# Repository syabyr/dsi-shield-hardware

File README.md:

# dsi-shield-hardware
dsi-shield hardware

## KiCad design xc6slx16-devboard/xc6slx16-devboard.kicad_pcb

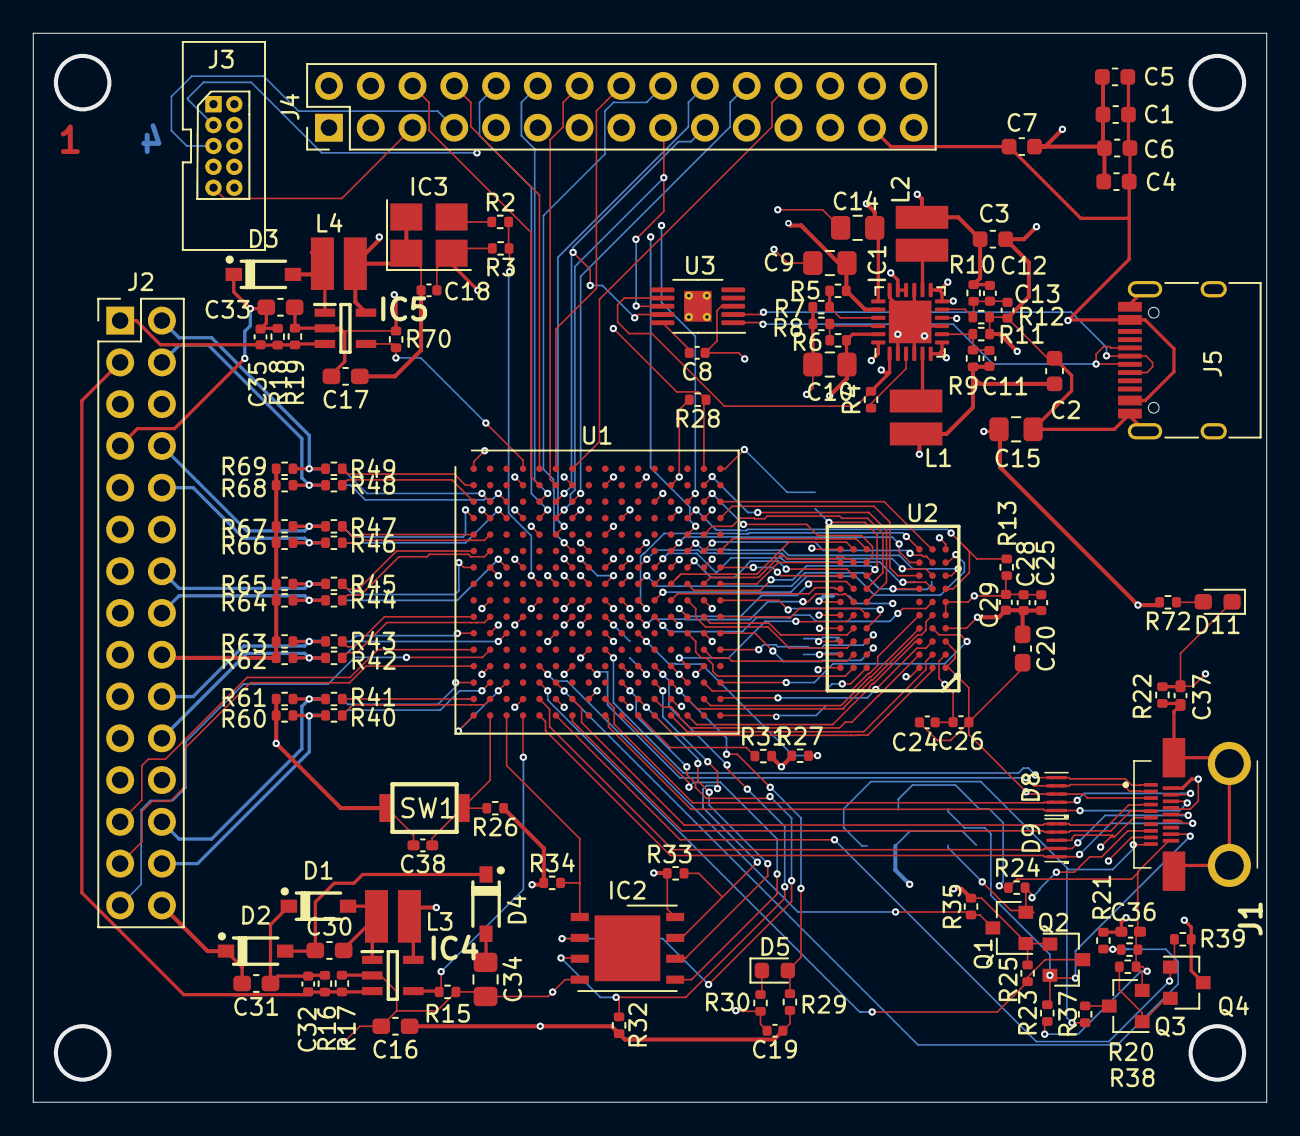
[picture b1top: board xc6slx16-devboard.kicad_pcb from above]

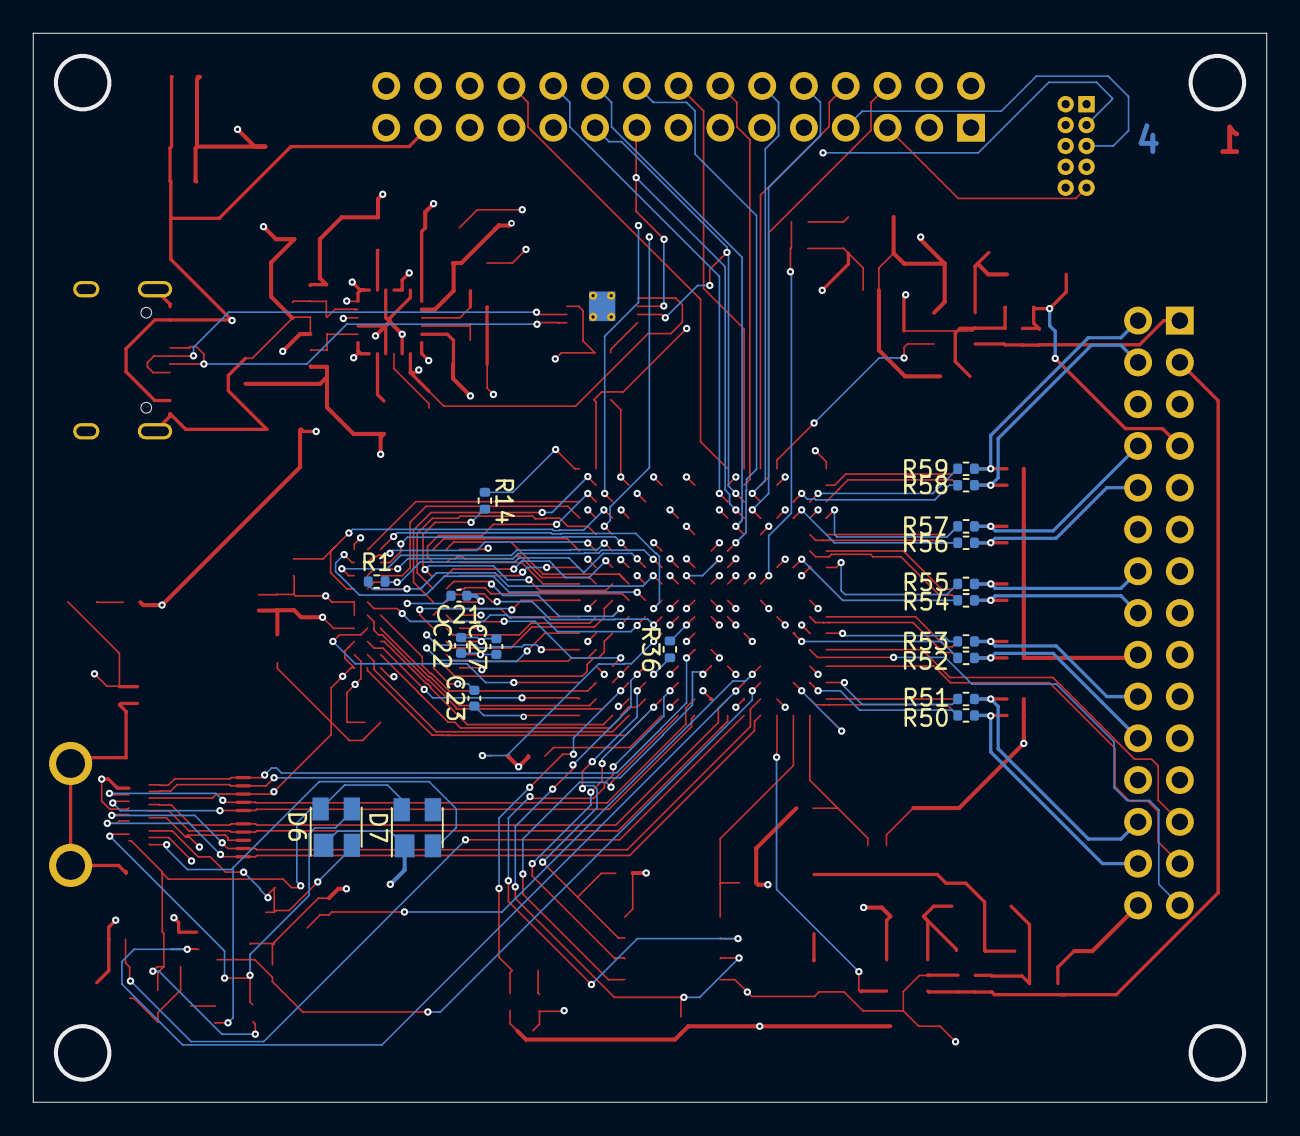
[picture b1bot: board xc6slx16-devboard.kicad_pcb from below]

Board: 4 copper layers, 75.0 x 65.0 mm, 141 parts (19 on the bottom side), 152 nets.

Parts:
C1, C2, C3, C6: 1u; C_0603_1608Metric
C4, C5: 4.7u; C_0603_1608Metric
C7: 10u; C_0603_1608Metric
C8, C18, C19, C21, C22, C23, C24, C25, C26: 100n; C_0402_1005Metric
C9, C10, C14, C15: 10u; C_0805_2012Metric_Pad1.18x1.45mm_HandSolder
C11: 8.2p; C_0402_1005Metric
C12: 6.8p; C_0402_1005Metric
C13: 33p; C_0402_1005Metric
C16, C17: 4.7u; C_0603_1608Metric_Pad1.08x0.95mm_HandSolder
C20, C30, C31, C33: 1u; C_0603_1608Metric_Pad1.08x0.95mm_HandSolder
C27, C28, C29: 10n; C_0402_1005Metric
C32, C35: 22p; C_0402_1005Metric
C34: 4.7u; C_0805_2012Metric_Pad1.18x1.45mm_HandSolder
C36, C37: 100n; C_0402_1005Metric_Pad0.74x0.62mm_HandSolder
C38: C; C_0402_1005Metric_Pad0.74x0.62mm_HandSolder
D1, D2, D3, D4: Diode_Schottky; SOD3715X145N
D5: LED; LED_0603_1608Metric
D6, D7: PRTR5V0U2X; SOT-143
D8, D9: IP4292CZ10; SOT1176-1
D11: LED; LED_0603_1608Metric_Pad1.05x0.95mm_HandSolder
IC1: LM26480; WQFN-24-1EP_4x4mm_P0.5mm_EP2.6x2.6mm
IC2: M25P80-VMN6P; DFN-8-1EP_6x5mm_P1.27mm_EP4x4mm
IC3: 25MHz; Oscillator_SMD_Abracon_ASE-4Pin_3.2x2.5mm_HandSoldering
IC4, IC5: SOT95P275X110-5N
J1: 10118241-001RLF; 10118241001RLF
J2, J4: Conn_02x15_Odd_Even; PinHeader_2x15_P2.54mm_Vertical
J3: Conn_02x05_Odd_Even; debugger_2x05_P1.27mm_Vertical
J5: USB_C
L1, L2: 2.2uH; IND_PANASONIC_ELLVEG
L3, L4: 4.7uH; IND_PANASONIC_ELLVEG
Q1, Q2, Q4: 2N7002; SOT-23
Q3: Q_BSS84; SOT-23
R1, R14: 100; R_0402_1005Metric
R2: 180; R_0402_1005Metric
R3: 220; R_0402_1005Metric
R4, R12, R15, R16, R18, R70: 100k; R_0402_1005Metric
R5: 280k; R_0402_1005Metric
R6: 750k; R_0402_1005Metric
R7: 200k; R_0402_1005Metric
R8: 187k; R_0402_1005Metric
R9: 464k; R_0402_1005Metric
R10: 560k; R_0402_1005Metric
R11: 178k; R_0402_1005Metric
R13: 4.7k; R_0402_1005Metric
R17, R19: 27k; R_0402_1005Metric
R20, R21, R23, R24, R25, R28, R35, R38, R39: 3.3k; R_0402_1005Metric
R22: 1M; R_0402_1005Metric
R26, R29, R30, R31, R36, R37, R72: 1k; R_0402_1005Metric
R27: 3k3; R_0402_1005Metric
R32, R33, R34: 10k; R_0402_1005Metric
R40, R41, R42, R43, R44, R45, R46, R47, R48, R49: 160; R_0402_1005Metric
R50, R51, R52, R53, R54, R55, R56, R57, R58, R59: 22; R_0402_1005Metric
R60, R61, R62, R63, R64, R65, R66, R67, R68, R69: 51; R_0402_1005Metric
SW1: SW_Push; turtlekey
U1: XC6SLX16-FTG256; Xilinx_FTG256
U2: K4X1G163PE; FBGA60-6X10
U3: CH340E; MSOP-10-1EP_3x3mm_P0.5mm_EP1.68x1.88mm_ThermalVias

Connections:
+1V2: C9.1, IC1.20, J4.23, R5.1, U1.G7, U1.G9, U1.H8, U1.H10, U1.J7, U1.J9, U1.K8, U1.K10
+2V5: C10.1, IC1.23, J2.21, J4.25, R6.1, U1.E5, U1.F8, U1.F11, U1.G10, U1.H6, U1.J10, U1.L6, U1.L9
+3V3: C3.1, C12.2, C15.1, C16.1, C17.1, C18.1, C19.1, IC1.24, IC2.8, IC3.1, IC3.4, IC4.5, IC5.5, J2.17, J2.23, J3.4, J4.4, J4.28, L2.2, L3.1, L4.1, Q1.1, Q2.1, R10.1, R25.1, R26.1, R27.1, R28.2, R29.2, R31.2, R32.2, R33.2, R34.1, R35.1, R72.2, U1.B4, U1.B9, U1.B13, U1.D7, U1.D10, U1.N7, U1.N10, U1.R4, U1.R8
+5V: C1.2, C4.1, C5.1, C6.2, C7.1, IC1.1, IC1.6, IC1.7, IC1.10, IC1.12, IC1.13, IC1.16, IC1.17, J4.3, J4.27, J5.A4, J5.A9, J5.B4, J5.B9, R4.2, U3.7
/hdmi-in/HPD_EN: Q4.1, R39.1, U1.T6
/hdmi-in/HPD_NOTIFY: R20.2, R21.1, U1.P6
/hdmi-in/SCL: Q2.3, R35.2, U1.N5
/hdmi-in/SDA: Q1.3, R25.2, U1.P5
/hdmi-in/TMDS0_N: D9.4, D9.7, J1.9, U1.T7
/hdmi-in/TMDS0_P: D9.5, D9.6, J1.7, U1.R7
/hdmi-in/TMDS1_N: D8.1, D8.10, J1.6, U1.T9
/hdmi-in/TMDS1_P: D8.2, D8.9, J1.4, U1.R9
/hdmi-in/TMDS2_N: D8.4, D8.7, J1.3, U1.N8
/hdmi-in/TMDS2_P: D8.5, D8.6, J1.1, U1.M9
/hdmi-in/TMDS_CLK_N: D9.1, D9.10, J1.12, U1.T5
/hdmi-in/TMDS_CLK_P: D9.2, D9.9, J1.10, U1.R5
/lpddrsdram/SDRAM_A0: U1.H15, U2.J8
/lpddrsdram/SDRAM_A1: U1.H16, U2.J9
/lpddrsdram/SDRAM_A2: U1.F16, U2.K7
/lpddrsdram/SDRAM_A3: U1.H13, U2.K8
/lpddrsdram/SDRAM_A4: U1.C16, U2.K2
/lpddrsdram/SDRAM_A5: U1.J11, U2.K3
/lpddrsdram/SDRAM_A6: U1.J12, U2.J1
/lpddrsdram/SDRAM_A7: U1.F15, U2.J2
/lpddrsdram/SDRAM_A8: U1.F13, U2.J3
/lpddrsdram/SDRAM_A9: U1.F14, U2.H1
/lpddrsdram/SDRAM_A10: U1.C15, U2.J7
/lpddrsdram/SDRAM_A11: U1.G11, U2.H2
/lpddrsdram/SDRAM_A12: U1.D16, U2.H3
/lpddrsdram/SDRAM_A13: U1.B15, U2.F7
/lpddrsdram/SDRAM_BA0: U1.G14, U2.H8
/lpddrsdram/SDRAM_BA1: U1.G16, U2.H9
/lpddrsdram/SDRAM_CAS_N: U1.K14, U2.G8
/lpddrsdram/SDRAM_CKE: R13.2, U1.D14, U2.G1
/lpddrsdram/SDRAM_CLK_N: R1.1, U1.H11, U2.G3
/lpddrsdram/SDRAM_CLK_P: R1.2, U1.G12, U2.G2
/lpddrsdram/SDRAM_CS_N: R14.2, U1.H14, U2.H7
/lpddrsdram/SDRAM_DQ0: U1.L14, U2.A8
/lpddrsdram/SDRAM_DQ1: U1.L16, U2.B7
/lpddrsdram/SDRAM_DQ2: U1.M15, U2.B8
/lpddrsdram/SDRAM_DQ3: U1.M16, U2.C7
/lpddrsdram/SDRAM_DQ4: U1.J14, U2.C8
/lpddrsdram/SDRAM_DQ5: U1.J16, U2.D7
/lpddrsdram/SDRAM_DQ6: U1.K15, U2.D8
/lpddrsdram/SDRAM_DQ7: U1.K16, U2.E7
/lpddrsdram/SDRAM_DQ8: U1.P15, U2.E3
/lpddrsdram/SDRAM_DQ9: U1.P16, U2.D2
/lpddrsdram/SDRAM_DQ10: U1.R15, U2.D3
/lpddrsdram/SDRAM_DQ11: U1.R16, U2.C2
/lpddrsdram/SDRAM_DQ12: U1.T14, U2.C3
/lpddrsdram/SDRAM_DQ13: U1.T13, U2.B2
/lpddrsdram/SDRAM_DQ14: U1.R12, U2.B3
/lpddrsdram/SDRAM_DQ15: U1.T12, U2.A2
/lpddrsdram/SDRAM_DQM0: U1.K11, U2.F8
/lpddrsdram/SDRAM_DQM1: U1.K12, U2.F2
/lpddrsdram/SDRAM_DQS0: U1.N14, U2.E8
/lpddrsdram/SDRAM_DQS1: U1.R14, U2.E2
/lpddrsdram/SDRAM_RAS_N: U1.J13, U2.G9
/lpddrsdram/SDRAM_WE_N: U1.E15, U2.G7
/power/BL_DIM: IC5.4, R70.1, U1.A4
/power/LCD_PWREN: IC4.4, R15.1, U1.T4
/xc6slx16/CLK_25MHZ: IC3.3, R2.1
/xc6slx16/FPGA_M0: R31.1, U1.T11
/xc6slx16/FPGA_M1: R36.1, U1.N11
/xc6slx16/QSPI_CLK: IC2.6, U1.R11
/xc6slx16/QSPI_CS0: IC2.1, R34.2, U1.T3
/xc6slx16/QSPI_DQ0: IC2.5, U1.T10
/xc6slx16/QSPI_DQ1: IC2.2, U1.P10
/xc6slx16/QSPI_DQ2: IC2.3, R32.1, U1.N12
/xc6slx16/QSPI_DQ3: IC2.7, R33.1, U1.P12
DBG_O0: J4.6, U1.B5
DBG_O1: J4.8, U1.A5
DBG_O2: J4.10, U1.D5
DBG_O3: J4.12, U1.C5
DBG_O4: J4.14, U1.B6
DBG_O5: J4.16, U1.A6
DBG_O6: J4.18, U1.F7
DBG_O7: J4.20, U1.E6
DBG_O8: J4.22, U1.C7
DBG_O9: J4.24, U1.A7
DBG_RX: J4.19, U1.C6, U3.9
DBG_TX: J4.17, U1.D6, U3.8
DSI_CLK_N: J2.14, R45.2, R55.2, R65.1
DSI_CLK_P: J2.16, R44.2, R54.2, R64.1
DSI_GPIO0: J2.27, U1.N1
DSI_GPIO1: J2.25, U1.M1
DSI_HS_0_N: R41.1, U1.R1
DSI_HS_0_P: R40.1, U1.R2
DSI_HS_1_N: R43.1, U1.K1
DSI_HS_1_P: R42.1, U1.K2
DSI_HS_2_N: R47.1, U1.E1
DSI_HS_2_P: R46.1, U1.E2
DSI_HS_3_N: R49.1, U1.B1
DSI_HS_3_P: R48.1, U1.C1
DSI_HS_CLK_N: R45.1, U1.F1
DSI_HS_CLK_P: R44.1, U1.F2
DSI_L0_N: J2.26, R41.2, R51.2, R61.1
DSI_L0_P: J2.28, R40.2, R50.2, R60.1
DSI_L1_N: J2.20, R43.2, R53.2, R63.1
DSI_L1_P: J2.22, R42.2, R52.2, R62.1
DSI_L2_N: J2.8, R47.2, R57.2, R67.1
DSI_L2_P: J2.10, R46.2, R56.2, R66.1
DSI_L3_N: J2.2, R49.2, R59.2, R69.1
DSI_L3_P: J2.4, R48.2, R58.2, R68.1
DSI_LP_0_N: R51.1, U1.P1
DSI_LP_0_P: R50.1, U1.P2
DSI_LP_1_N: R53.1, U1.L1
DSI_LP_1_P: R52.1, U1.L3
DSI_LP_2_N: R57.1, U1.D1
DSI_LP_2_P: R56.1, U1.D3
DSI_LP_3_N: R59.1, U1.C2
DSI_LP_3_P: R58.1, U1.C3
DSI_LP_CLK_N: R55.1, U1.G1
DSI_LP_CLK_P: R54.1, U1.G3
DSI_RESET_N: J2.29, U1.M2
FPGA_TCK: J3.1, J4.11, U1.C14
FPGA_TDI: J3.9, J4.5, U1.C12
FPGA_TDO: J3.3, J4.9, U1.E14
FPGA_TMS: J3.5, J4.7, R28.1, U1.A15
GND: C1.1, C2.2, C3.2, C4.2, C5.2, C6.1, C7.2, C8.1, C9.2, C10.2, C13.2, C14.2, C15.2, C16.2, C17.2, C18.2, C19.2, C20.2, C21.2, C22.1, C23.1, C24.1, C25.1, C26.1, C27.1, C28.1, C29.1, C31.2, C33.2, C34.2, C36.2, C37.2, C38.2, D2.1, D6.1, D7.1, D8.3, D8.8, D9.3, D9.8, D11.1, IC1.2, IC1.4, IC1.9, IC1.15, IC1.18, IC1.25, IC2.4, IC3.2, IC4.2, IC5.2, J1.2, J1.5, J1.8, J1.11, J1.17, J2.5, J2.6, J2.9, J2.11, J2.12, J2.18, J2.24, J2.30, J3.2, J3.10, J4.1, J4.2, J4.21, J4.29, J4.30, J5.A1, J5.A12, J5.B1, J5.B12, J5.S1, Q4.3, R3.2, R7.2, R8.2, R11.2, R12.2, R13.1, R14.1, R15.2, R17.2, R19.2, R21.2, R22.1, R30.1, R36.2, R39.2, R60.2, R61.2, R62.2, R63.2, R64.2, R65.2, R66.2, R67.2, R68.2, R69.2, R70.2, SW1.1, U1.A1, U1.A16, U1.B7, U1.B11, U1.D4, U1.D13, U1.E9, U1.G2, U1.G8, U1.G15, U1.H7, U1.H9, U1.H12, U1.J5, U1.J8, U1.K7, U1.K9, U1.L2, U1.L15, U1.M8, U1.N13, U1.P3, U1.P14, U1.R6, U1.R10, U1.T1, U1.T16, U2.A1, U2.A3, U2.B9, U2.C1, U2.D9, U2.E1, U2.F1, U2.K1, U3.3
HDMI_HPD: D7.2, J1.19, R37.1
HDMI_P5V: C36.1, D6.4, D7.4, J1.18, Q3.2, R20.1, R23.1, R24.1, R38.1
HDMI_SCL: D6.2, J1.15, Q2.2, R24.2
HDMI_SDA: D6.3, J1.16, Q1.2, R23.2
LCD_BL_A: C33.1, C35.1, D3.1, J2.7, R18.1
LCD_BL_FB: C35.2, IC5.3, J2.1, R18.2, R19.1
LCD_BOOST_FB: C32.2, IC4.3, J2.3, R16.2, R17.1
LCD_MVDD: C34.1, D4.2
LCD_PVDD: C31.1, C32.1, D1.1, R16.1
unnamed: C8.2, U3.10
unnamed: C11.1, IC1.8, R9.2, R11.1
unnamed: C12.1, C13.1, IC1.11, R10.2, R12.1
unnamed: C30.1, D2.2, D4.1
unnamed: C30.2, D1.2, IC4.1, L3.2
unnamed: C37.1, J1.MH1, J1.MH2, J1.MP1, J1.MP2, R22.2
unnamed: C38.1, R26.2, SW1.2, U1.T2
unnamed: D3.2, IC5.1, L4.2
unnamed: D5.1, R30.2
unnamed: D5.2, R29.1, U1.P13
unnamed: D11.2, R72.1
unnamed: IC1.3, R4.1
unnamed: IC1.5, L1.1
unnamed: IC1.14, L2.1
unnamed: IC1.21, R5.2, R7.1
unnamed: IC1.22, R6.2, R8.1
unnamed: J5.A6, J5.B6, U3.1
unnamed: J5.A7, J5.B7, U3.2
unnamed: Q3.1, Q4.2, R38.2
unnamed: Q3.3, R37.2
unnamed: R2.2, R3.1, U1.H5
unnamed: R27.2, U1.L11
V_DDR: C2.1, C11.2, C14.1, C20.1, C21.1, C22.2, C23.2, C24.2, C25.2, C26.2, C27.2, C28.2, C29.2, IC1.19, J2.19, J4.26, L1.2, R9.1, U1.D2, U1.D15, U1.G4, U1.G13, U1.J2, U1.J15, U1.K4, U1.K13, U1.N2, U1.N15, U1.R13, U2.A7, U2.A9, U2.B1, U2.C9, U2.D1, U2.E9, U2.F9, U2.K9

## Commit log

2020-11-29 devboard
2020-11-29 20201130
2020-12-04 20201204
2020-12-06 20201205
2020-12-07 8/18
2020-12-08 gerber
2020-12-27 xc6slx16-rev2
2021-01-16 rev2
2021-01-16 rev1 backup
2021-01-16 sync rev1
